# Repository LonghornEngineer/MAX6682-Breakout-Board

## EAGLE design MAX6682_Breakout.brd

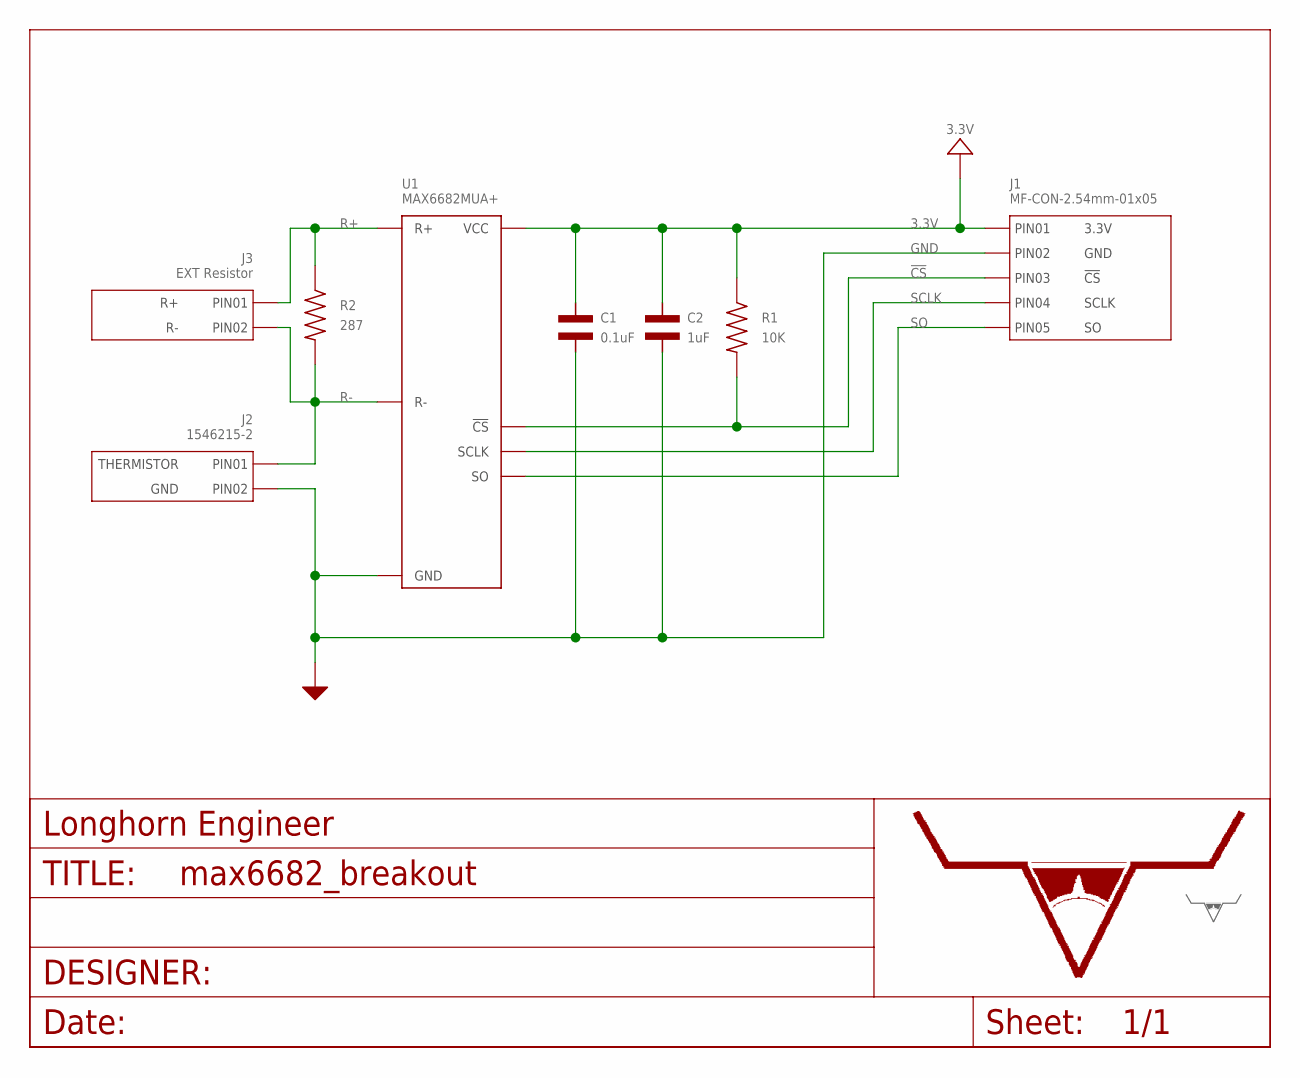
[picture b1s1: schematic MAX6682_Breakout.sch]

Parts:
C1: 0.1uF; C0603
C2: 1uF; C0603
J1: MF-CON-2.54mm-01x05; PTH_2.54MM_01X05
J2: 1546215-2
J3: EXT Resistor; 2.54MM_01X02_PIN_HEADER
R1: 10K; R0603
R2: 287; R0603; MPN ERA-3AEB2870V
U1: MAX6682MUA+; MAX6682_UMAX-8
U$7: LHE_FRAME
U$8: LHE_LOGOLHE_LOGO; LHE_LOGO

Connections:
3.3V: C1.P$1, C2.P$1, J1.P$1 (PIN1), R1.P$1, U1.P$8 (VCC)
!CS: J1.P$3 (PIN3), R1.P$2, U1.P$5 (!CS)
GND: C1.P$2, C2.P$2, J1.P$2 (PIN2), J2.P$2 (PIN2), U1.P$4 (GND)
R+: J3.1 (PIN1), R2.P$1, U1.P$2 (R+)
R-: J2.P$1 (PIN1), J3.2 (PIN2), R2.P$2, U1.P$3 (R-)
SCLK: J1.P$4 (PIN4), U1.P$7 (SCLK)
SO: J1.P$5 (PIN5), U1.P$6 (SO)

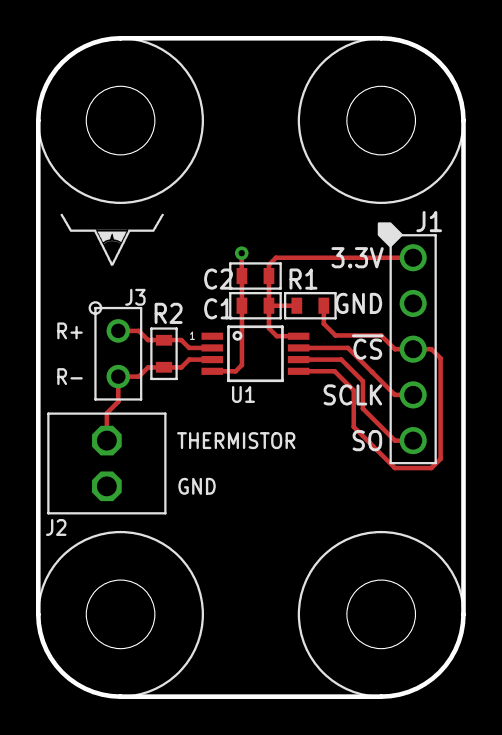
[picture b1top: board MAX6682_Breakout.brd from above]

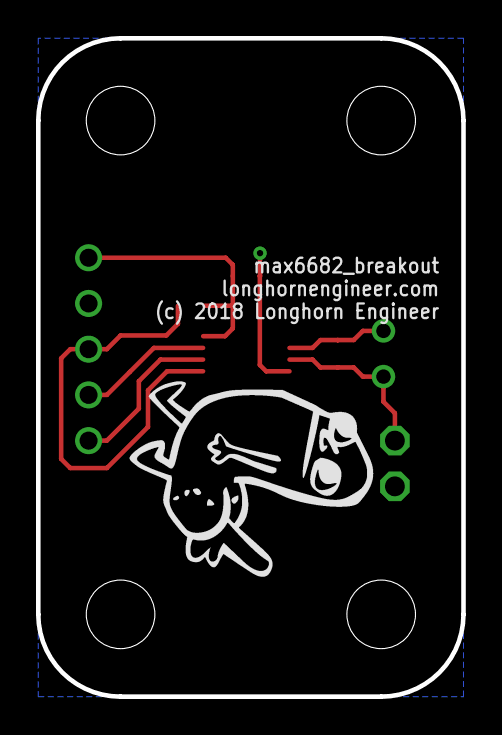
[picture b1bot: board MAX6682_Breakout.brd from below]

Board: 2 copper layers, 23.6 x 36.6 mm, 15 parts (2 on the bottom side), 7 nets.

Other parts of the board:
U$3, U$4, U$5, U$6: MOUNT_HOLE_150MIL
U$9: DB_SILK_MEDIUM

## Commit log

2018-06-25 Fist rev and associated files

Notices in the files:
parts and their libraries:
PP_Aesthetics: (c) 2018 Longhorn Engineer
